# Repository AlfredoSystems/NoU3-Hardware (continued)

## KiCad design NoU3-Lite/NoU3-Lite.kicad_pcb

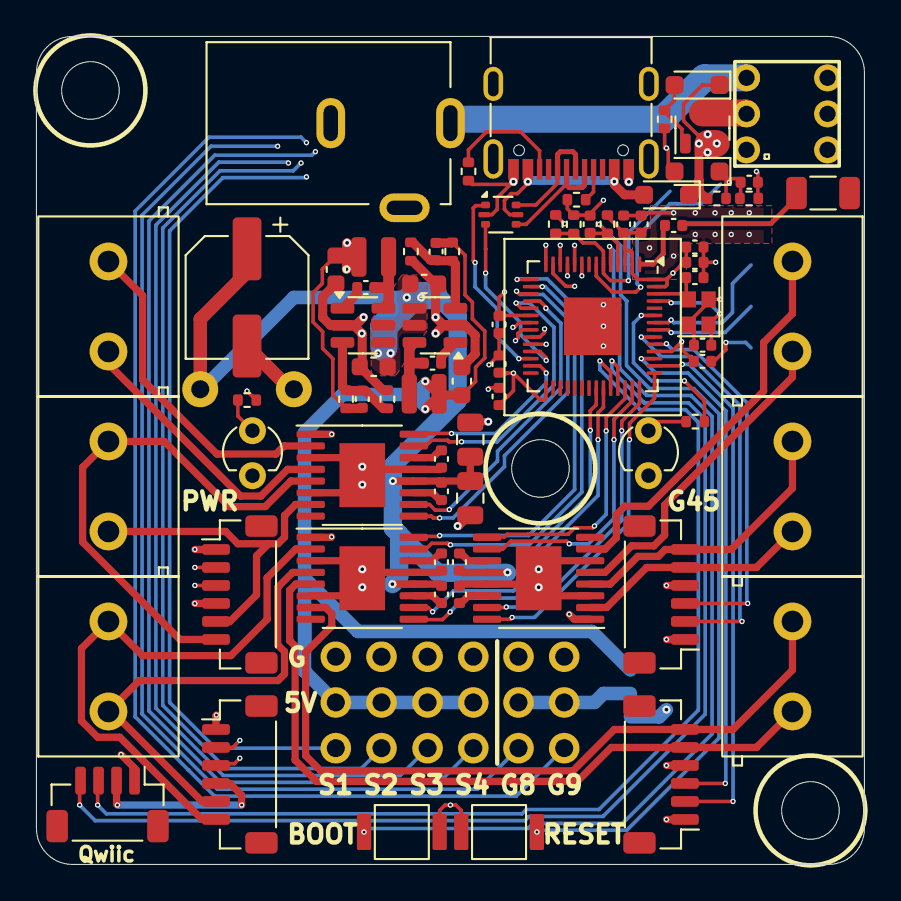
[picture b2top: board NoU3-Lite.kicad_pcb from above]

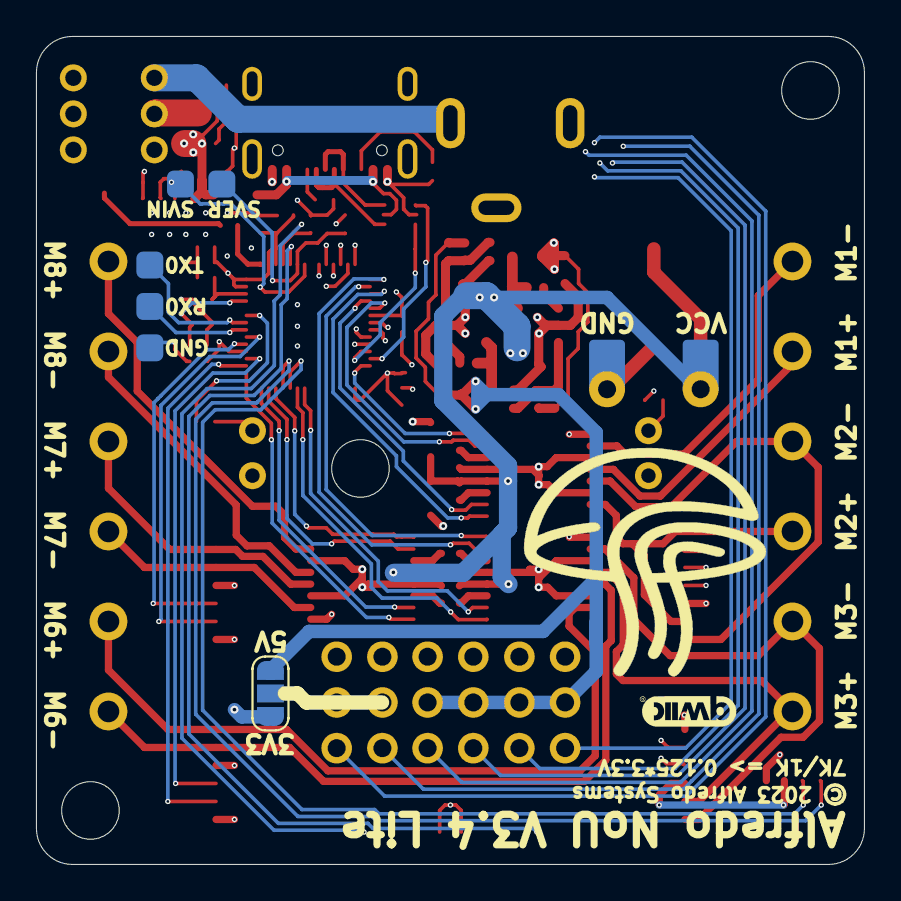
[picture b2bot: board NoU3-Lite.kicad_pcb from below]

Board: 4 copper layers, 46.0 x 46.0 mm, 92 parts (8 on the bottom side), 80 nets.

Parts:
C1, C15, C25, C26, C28, C29, C30: 100nF; C_0402_1005Metric
C3, C6, C9, C34: 10nF; C_0402_1005Metric
C4, C7, C10: 2.2uF; C_0402_1005Metric
C5, C8: 10uF; C_0805_2012Metric
C14: 100pF; C_0402_1005Metric
C16: CP_Elec_6.3x7.7
C21: 10uF; C_0402_1005Metric
C22, C23: 10uF,25V; C_0603_1608Metric
C24, C27, C31: 1uF; C_0402_1005Metric
C32, C33, C37, C38: 10pF; C_0402_1005Metric
C35, C36: 22uF, 6V3; C_0603_1608Metric
D1: Z5V6; D_SOD-323
D2: 1N5819; D_SOD-323
D3: Z3V3; D_SOD-323
D5: LED_blue; LED_3mm
D6: LED_green; LED_3mm
J1, J4, J7, J17: JST SR/SZ; JST_SH_1x06_Vertical
J2, J3, J5, J6, J8, J9: Screw_Terminal_01x02; TerminalBlock_Ningbo_2P_5mm
J14: RFANT3216120A5T; C_1206_3216Metric
J15: Barrel_Jack; DC-005C_1
J16: VIN; PinSocket_1x01_P2.54mm_Vertical
J18: GND; PinSocket_1x01_P2.54mm_Vertical
JP1: Jumper_3_Open; SolderJumper-3-Small
L1, L2: 4.7uH; LVF252A12
Q1: AO3401A; SOT-23-small
R5, R17, R18, R29: 1K; R_0402_1005Metric
R10: 10K; R_0402_1005Metric
R11: 68K; R_0402_1005Metric
R12, R26: 15K; R_0402_1005Metric
R13: 33K; R_0402_1005Metric
R14: 4K7; R_0402_1005Metric
R15, R16: 5.1K; R_0402_1005Metric
R27: 2K2; R_0402_1005Metric
R30: 6K8; R_0402_1005Metric
SW1: reset; Button_SKRKAEE020
SW2: boot; Button_SKRKAEE020
T1, T1#2, T1#3, T1#4: Tab
TP1: RX0; PogoPad1
TP2: TX0; PogoPad1
TP3: GND; PogoPad1
TP20: Svin; PogoPad1
TP21: Sver; PogoPad1
U1, U4, U5: HR8833
U2: ESP32-S3FN8; QFN-56-1EP_7x7mm_P0.4mm_EP3.2x3.2mm
U3: Crystal_ESP32; Crystal_SMD_2016-4Pin_2.0x1.6mm
U7, U18, U19: ServoPorts_2x3
U8: 5.8 ZSPT; XKB5858-Z-75
U9: USBLC6-2P6; SOT-666
U11: Qwiic1; JST_SH_BM04B-SRSS-TB_1x04-1MP_P1.00mm_Vertical
U15, U16: SY8113BADC; TSOT-23-6
U17: USB_C_Receptacle; USB_TYPE-C-31-M-12

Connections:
+3V3: C21.2, C24.2, C25.2, C26.2, C27.2, C30.2, C31.2, C32.1, C34.2, C35.1, J1.4, J4.4, J7.4, J17.4, JP1.1 (A), L1.2, R5.2, R11.1, R17.1, R30.2, U1.1 (nSLEEP), U2.2 (VDD3P3), U2.3 (VDD3P3), U2.20 (VDD3P3_RTC), U2.29 (VDDSPI), U2.46 (VDD3P3_CPU), U2.55 (VDDA), U2.56 (VDDA), U4.1 (nSLEEP), U5.1 (nSLEEP), U11.2 (3V3)
+5V: C33.1, C36.1, JP1.3 (B), L2.2, R13.1, U18.1 (PWR), U19.1 (PWR)
/MotorDriver-1/Aout1: J1.5, J2.2, U1.2 (AOUT1)
/MotorDriver-1/Aout2: J1.6, J2.1, U1.4 (AOUT2)
/MotorDriver-1/Bout1: J3.1, U1.7 (BOUT1)
/MotorDriver-1/Bout2: J3.2, U1.5 (BOUT2)
/MotorDriver-2/Aout1: J5.2, U4.2 (AOUT1)
/MotorDriver-2/Aout2: J5.1, U4.4 (AOUT2)
/MotorDriver-2/Bout1: J4.5, J6.1, U4.7 (BOUT1)
/MotorDriver-2/Bout2: J4.6, J6.2, U4.5 (BOUT2)
/MotorDriver-3/Aout1: J7.6, J8.2, U5.2 (AOUT1)
/MotorDriver-3/Aout2: J7.5, J8.1, U5.4 (AOUT2)
/VUSB: D2.2 (A), U9.5 (VBUS), U17.A4 (VBUS), U17.A9 (VBUS), U17.B4 (VBUS), U17.B9 (VBUS)
E2A: J4.3, U2.21 (XTAL32K_P)
E2B: J4.2, U2.22 (XTAL_32K_N)
E3A: J7.3, U2.23 (GPIO17/DAC_1)
E3B: J7.2, U2.24 (GPIO18/DAC_2)
E4A: J17.3, U2.45 (MTDO)
E4B: J17.2, U2.44 (MTCK)
E5A: J1.3, U2.47 (MTDI)
E5B: J1.2, U2.48 (MTMS)
E_D+: U2.26 (GPIO20), U9.1 (I/O1)
E_D-: U2.25 (GPIO19), U9.3 (I/O2)
GND: C1.2, C4.2, C5.2, C7.2, C8.2, C10.2, C15.2, C16.2, C21.1, C22.2, C23.2, C24.1, C25.1, C26.1, C27.1, C30.1, C31.1, C34.1, C35.2, C36.2, C37.2, C38.1, D3.2 (A), D5.1 (K), D6.1 (K), J1.1, J4.1, J7.1, J15.2, J17.1, J18.1, R10.2, R12.2, R14.2, R15.2, R16.1, R27.1, R29.1, SW1.2, SW2.2, TP3.1, U1.3 (AISEN), U1.6 (BISEN), U1.13 (GND), U1.17 (GND(PPAD)), U2.57 (EPAD), U3.2, U3.4, U4.3 (AISEN), U4.6 (BISEN), U4.13 (GND), U4.17 (GND(PPAD)), U5.3 (AISEN), U5.6 (BISEN), U5.13 (GND), U5.17 (GND(PPAD)), U7.2 (GND), U9.2 (GND), U11.1 (GND), U15.2 (GND), U16.2 (GND), U17.A1 (GND), U17.A12 (GND), U17.B1 (GND), U17.B12 (GND), U18.2 (GND), U19.2 (GND)
GPIO_MISC1: U2.13 (GPIO8), U7.3 (srv1)
GPIO_MISC2: U2.14 (GPIO9), U7.4 (srv2)
LED_MISC: R18.1, U2.51 (GPIO45)
M1A: U2.27 (GPIO21), U4.16 (AIN1)
M1B: U2.19 (GPIO14), U4.15 (AIN2)
M2A: U2.17 (GPIO12), U4.9 (BIN1)
M2B: U2.18 (GPIO13), U4.10 (BIN2)
M3A: U2.16 (GPIO11), U5.16 (AIN1)
M3B: U2.15 (GPIO10), U5.15 (AIN2)
M4A: U2.37 (SPICLK_P), U5.9 (BIN1)
M4B: U2.36 (SPICLK_N), U5.10 (BIN2)
M5A: U1.16 (AIN1), U2.43 (GPIO38)
M5B: U1.15 (AIN2), U2.42 (GPIO37)
M6A: U1.9 (BIN1), U2.40 (GPIO35)
M6B: U1.10 (BIN2), U2.41 (GPIO36)
MD4_B1: J9.1, J17.6, U5.7 (BOUT1)
MD4_B2: J9.2, J17.5, U5.5 (BOUT2)
unnamed: D1.2 (A), Q1.1 (G), R10.1
unnamed: D5.2 (A), R17.2
unnamed: D6.2 (A), R18.2
unnamed: C14.1, J14.1 (FEED)
unnamed: J15.1, U8.3
unnamed: JP1.2 (C), U7.1 (PWR)
unnamed: Q1.3 (D), U8.2
unnamed: C3.2, U1.11 (VCP)
unnamed: C4.1, U1.14 (VINT)
unnamed: C1.1, R5.1, SW1.1, U2.4 (CHIP_PU)
unnamed: SW2.1, U2.5 (GPIO0)
unnamed: C14.2, U2.1 (LNA_IN)
unnamed: TP2.1, U2.50 (U0RXD)
unnamed: TP1.1, U2.49 (U0TXD)
unnamed: C38.2, U2.53 (XTAL_N), U3.1
unnamed: C37.1, U2.54 (XTAL_P), U3.3
unnamed: C6.2, U4.11 (VCP)
unnamed: C7.1, U4.14 (VINT)
unnamed: C9.2, U5.11 (VCP)
unnamed: C10.1, U5.14 (VINT)
unnamed: C28.1, U15.1 (BS)
unnamed: C32.2, R11.2, R12.1, U15.3 (FB)
unnamed: C28.2, L1.1, U15.6 (LX)
unnamed: C29.1, U16.1 (BS)
unnamed: C33.2, R13.2, R14.1, U16.3 (FB)
unnamed: C29.2, L2.1, U16.6 (LX)
unnamed: R15.1, U17.A5 (CC1)
unnamed: R16.2, U17.B5 (CC2)
unnamed: U9.6 (I/O1), U17.A6 (D+), U17.B6 (D+)
unnamed: U9.4 (I/O2), U17.A7 (D-), U17.B7 (D-)
Q_SCL: U2.39 (GPIO34), U11.4 (SCL)
Q_SDA: U2.38 (GPIO33), U11.3 (SDA)
SNS_VER: R29.2, R30.1, TP21.1, U2.6 (GPIO1)
SNS_VIN: C15.1, D3.1 (K), R26.1, R27.2, TP20.1, U2.7 (GPIO2)
SRV1: U2.9 (GPIO4), U18.3 (srv1)
SRV2: U2.10 (GPIO5), U18.4 (srv2)
SRV3: U2.11 (GPIO6), U19.3 (srv1)
SRV4: U2.12 (GPIO7), U19.4 (srv2)
VCC: C3.1, C5.1, C6.1, C8.1, C9.1, C16.1, C22.1, C23.1, D1.1 (K), D2.1 (K), J16.1, Q1.2 (S), R26.2, U1.12 (VM), U4.12 (VM), U5.12 (VM), U15.4 (EN), U15.5 (IN), U16.4 (EN), U16.5 (IN)

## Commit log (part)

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2023-03-30 NoU3 initial commit and first board revision
2023-07-27 locked in mag and 6dof sensor for this rev
2023-07-27 vin sns and version sns dividers
2023-07-29 finished main changes, just need to route now
2023-07-30 routing half finished
2023-07-30 finished routing, ran DRC, fixed all the important DRC errors
2023-08-09 NoU3 as ordered 8/7/23
2023-10-09 updated date
2023-12-11 added jst CAD
2024-04-27 updated todo
2024-05-06 updated notes
2024-05-15 initial V3.2 changes
2024-05-16 order candidate, layout complete
2024-05-30 used a different fabrication tool
2024-07-02 Ordered NoU3.3 and 3.4 lite
2024-08-16 rule and schematic tweaks
2024-10-03 Schematic cleanup and plotted PDF
2025-04-03 updated labels
2025-04-10 commit before updating to kicad 9
2025-04-10 updated for kicad 9
2025-04-28 panalized for latest order
2025-07-18 Update wiring and remove unused junctions in schematic
2025-10-22 first commit for V3.4 changes
2025-11-05 bumped version to NoU3.5
2025-11-05 removed mag sensor, improved regulator resistor values
2025-11-06 added 7th encoder, 2nd 220uf cap
2025-11-06 NoU3.5s as ordered 11/6/25
2025-11-25 first commit for NoU3.6
2025-11-26 Update LSM6DS3TR-C part and add PCB silk circle
    Changed the schematic part value, datasheet, and LCSC code from LSM6DSDTR to LSM6DS3TR-C. Added a new circle to the F.SilkS layer in the PCB. Removed the auto-saved files reference.
2025-11-26 Fixed polarity convention for encoder port 1
2025-12-02 Swap positions of MD2_A1 and MD2_A2 labels
2026-03-25 Adjust component positions, silkscreen and traces
